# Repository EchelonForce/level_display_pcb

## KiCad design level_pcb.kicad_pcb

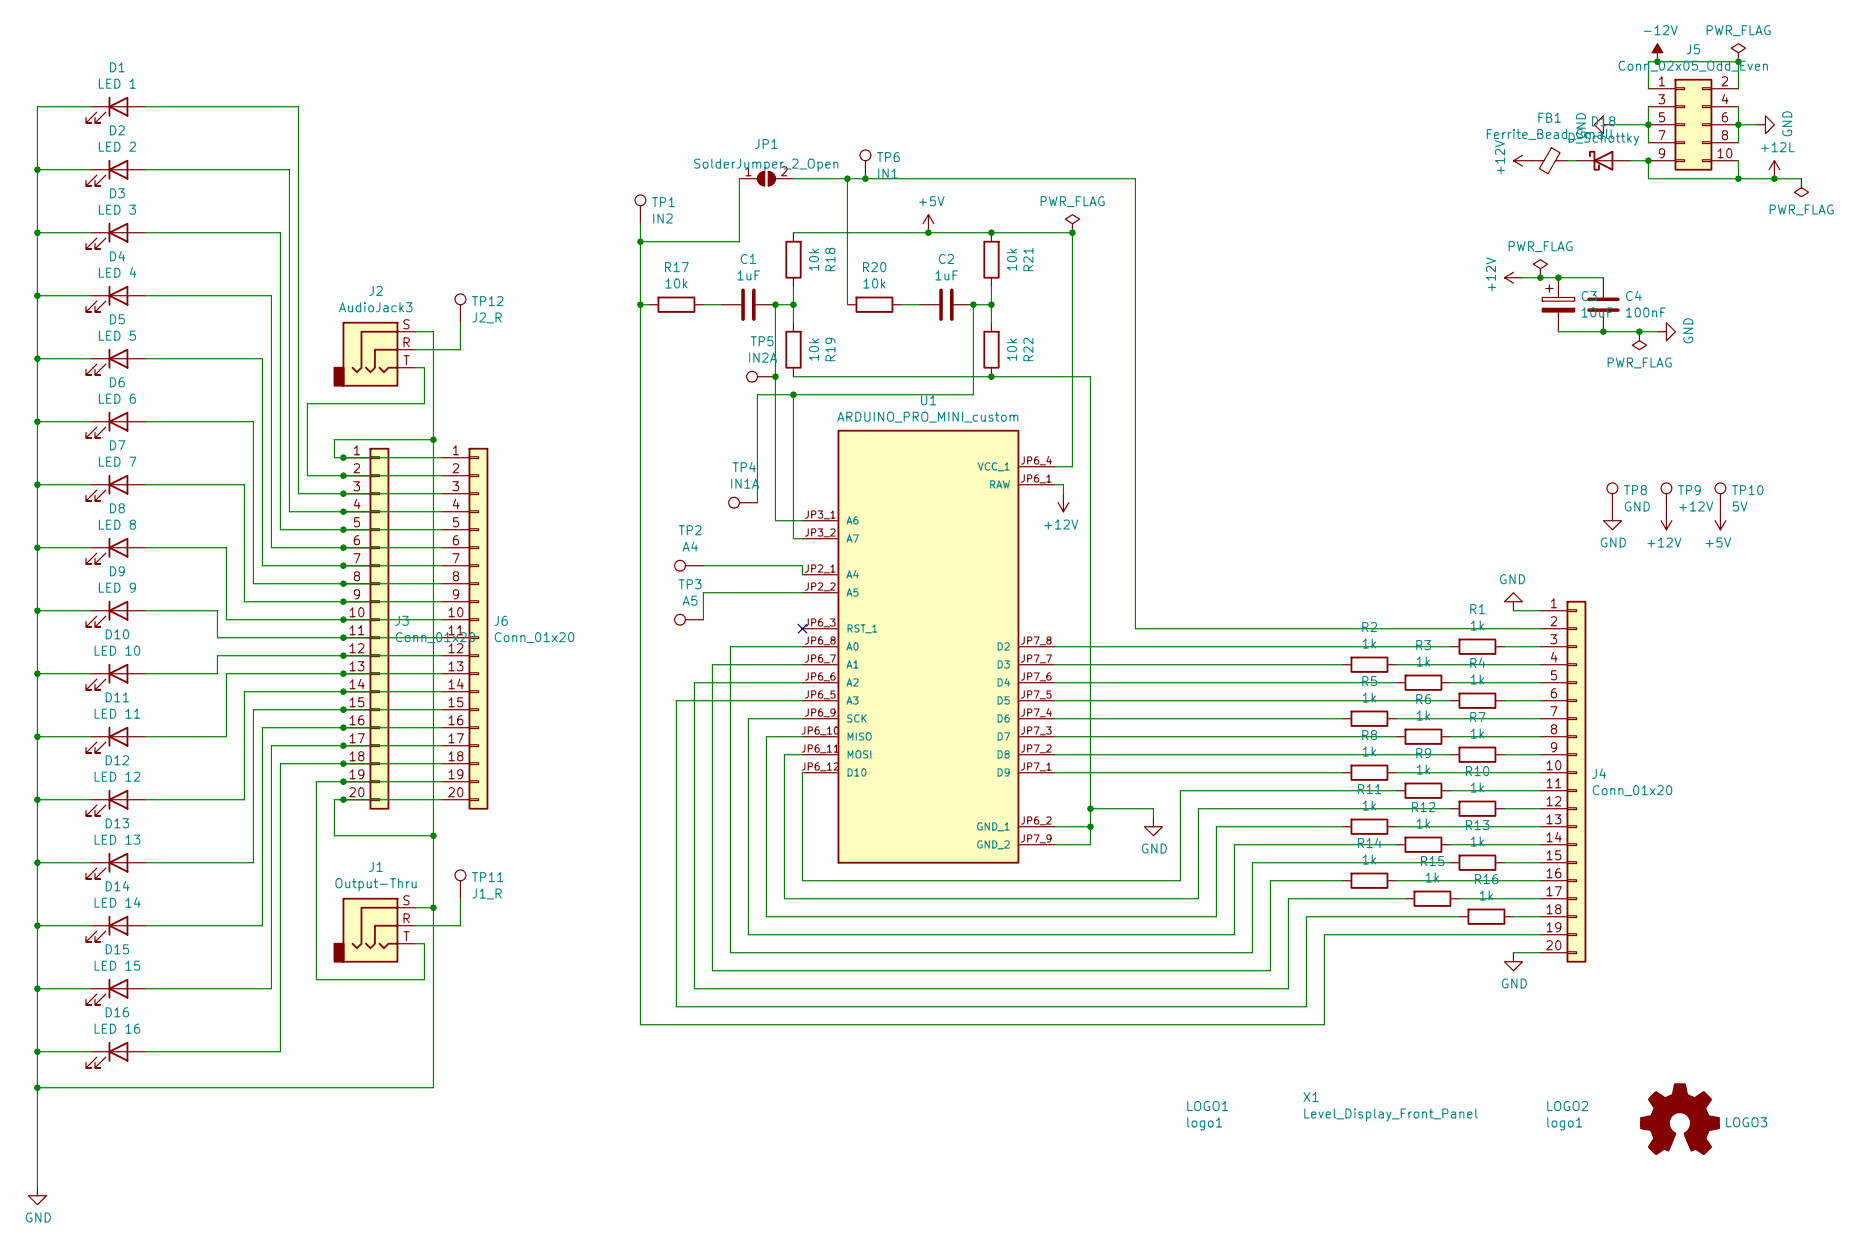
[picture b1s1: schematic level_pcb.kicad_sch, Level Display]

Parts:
C1, C2: 1uF; C_Disc_D6.0mm_W4.4mm_P5.00mm
C3: 10uF; CP_Radial_D5.0mm_P2.50mm
C4: 100nF; C_Disc_D6.0mm_W4.4mm_P5.00mm
D1: LED 1; LED_D3.0mm
D2: LED 2; LED_D3.0mm
D3: LED 3; LED_D3.0mm
D4: LED 4; LED_D3.0mm
D5: LED 5; LED_D3.0mm
D6: LED 6; LED_D3.0mm
D7: LED 7; LED_D3.0mm
D8: LED 8; LED_D3.0mm
D9: LED 9; LED_D3.0mm
D10: LED 10; LED_D3.0mm
D11: LED 11; LED_D3.0mm
D12: LED 12; LED_D3.0mm
D13: LED 13; LED_D3.0mm
D14: LED 14; LED_D3.0mm
D15: LED 15; LED_D3.0mm
D16: LED 16; LED_D3.0mm
D18: D_Schottky; D_DO-15_P10.16mm_Horizontal
FB1: Ferrite_Bead_Small; L_Axial_L7.0mm_D3.3mm_P5.08mm_Vertical_Fastron_MICC
J1: Output-Thru; Jack_2.5mm_MJ-355W_Vertical
J2: AudioJack3; Jack_2.5mm_MJ-355W_Vertical
J3, J6: Conn_01x20; PinHeader_1x20_P2.54mm_Vertical
J4: Conn_01x20; PinSocket_1x20_P2.54mm_Horizontal
J5: Conn_02x05_Odd_Even; IDC-Header_2x05_P2.54mm_Horizontal
JP1: SolderJumper_2_Open; SolderJumper-2_P1.3mm_Open_Pad1.0x1.5mm
LOGO1, LOGO2: logo1; Logo1
LOGO3: Logo_Open_Hardware_Small; OSHW-Symbol_6.7x6mm_SilkScreen
R1, R2, R3, R4, R5, R6, R7, R8, R9, R10, R11, R12, R13, R14, R15, R16: 1k; R_Axial_DIN0204_L3.6mm_D1.6mm_P7.62mm_Horizontal
R17, R18, R19, R20, R21, R22: 10k; R_Axial_DIN0204_L3.6mm_D1.6mm_P7.62mm_Horizontal
TP1: IN2; TestPoint_THTPad_D2.5mm_Drill1.2mm
TP2: A4; TestPoint_THTPad_D2.5mm_Drill1.2mm
TP3: A5; TestPoint_THTPad_D2.5mm_Drill1.2mm
TP4: IN1A; TestPoint_THTPad_D2.5mm_Drill1.2mm
TP5: IN2A; TestPoint_THTPad_D2.5mm_Drill1.2mm
TP6: IN1; TestPoint_THTPad_D2.5mm_Drill1.2mm
TP8: GND; TestPoint_THTPad_2.5x2.5mm_Drill1.2mm
TP9: +12V; TestPoint_THTPad_D2.5mm_Drill1.2mm
TP10: 5V; TestPoint_THTPad_D2.5mm_Drill1.2mm
TP11: J1_R; TestPoint_THTPad_D2.5mm_Drill1.2mm
TP12: J2_R; TestPoint_THTPad_D2.5mm_Drill1.2mm
U1: ARDUINO_PRO_MINI_custom; MODULE_ARDUINO_PRO_MINI_custom; PARTREV N/A
X1: Level_Display_Front_Panel

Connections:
+5V: R18.2, R21.2, TP10.1, U1.JP6_4 (VCC_1)
+12L: D18.2 (A), J5.9, J5.10
+12V: C3.1, C4.2, FB1.2, TP9.1, U1.JP6_1 (RAW)
-12V: J5.1, J5.2
GND: C3.2, C4.1, D1.1 (K), D2.1 (K), D3.1 (K), D4.1 (K), D5.1 (K), D6.1 (K), D7.1 (K), D8.1 (K), D9.1 (K), D10.1 (K), D11.1 (K), D12.1 (K), D13.1 (K), D14.1 (K), D15.1 (K), D16.1 (K), J1.S, J2.S, J3.1, J3.20, J4.1, J4.20, J5.3, J5.4, J5.5, J5.6, J5.7, J5.8, J6.1, J6.20, R19.1, R22.1, TP8.1, U1.JP6_2 (GND_1), U1.JP7_9 (GND_2)
unnamed: C1.1, R18.1, R19.2, TP5.1, U1.JP3_1 (A6)
unnamed: C1.2, R17.1
unnamed: C2.1, R21.1, R22.2, TP4.1, U1.JP3_2 (A7)
unnamed: C2.2, R20.1
unnamed: D1.2 (A), J3.3, J6.3
unnamed: D2.2 (A), J3.4, J6.4
unnamed: D3.2 (A), J3.5, J6.5
unnamed: D4.2 (A), J3.6, J6.6
unnamed: D5.2 (A), J3.7, J6.7
unnamed: D6.2 (A), J3.8, J6.8
unnamed: D7.2 (A), J3.9, J6.9
unnamed: D8.2 (A), J3.10, J6.10
unnamed: D9.2 (A), J3.11, J6.11
unnamed: D10.2 (A), J3.12, J6.12
unnamed: D11.2 (A), J3.13, J6.13
unnamed: D12.2 (A), J3.14, J6.14
unnamed: D13.2 (A), J3.15, J6.15
unnamed: D14.2 (A), J3.16, J6.16
unnamed: D15.2 (A), J3.17, J6.17
unnamed: D16.2 (A), J3.18, J6.18
unnamed: D18.1 (K), FB1.1
unnamed: J1.R, TP11.1
unnamed: J1.T, J3.19, J6.19
unnamed: J2.R, TP12.1
unnamed: J2.T, J3.2, J6.2
unnamed: J4.2, JP1.2 (B), R20.2, TP6.1
unnamed: J4.3, R1.1
unnamed: J4.4, R2.1
unnamed: J4.5, R3.1
unnamed: J4.6, R4.1
unnamed: J4.7, R5.1
unnamed: J4.8, R6.1
unnamed: J4.9, R7.1
unnamed: J4.10, R8.1
unnamed: J4.11, R9.1
unnamed: J4.12, R10.1
unnamed: J4.13, R11.1
unnamed: J4.14, R12.1
unnamed: J4.15, R13.1
unnamed: J4.16, R14.1
unnamed: J4.17, R15.1
unnamed: J4.18, R16.1
unnamed: J4.19, JP1.1 (A), R17.2, TP1.1
unnamed: R1.2, U1.JP7_8 (D2)
unnamed: R2.2, U1.JP7_7 (D3)
unnamed: R3.2, U1.JP7_6 (D4)
unnamed: R4.2, U1.JP7_5 (D5)
unnamed: R5.2, U1.JP7_4 (D6)
unnamed: R6.2, U1.JP7_3 (D7)
unnamed: R7.2, U1.JP7_2 (D8)
unnamed: R8.2, U1.JP7_1 (D9)
unnamed: R9.2, U1.JP6_12 (D10)
unnamed: R10.2, U1.JP6_11 (MOSI)
unnamed: R11.2, U1.JP6_10 (MISO)
unnamed: R12.2, U1.JP6_9 (SCK)
unnamed: R13.2, U1.JP6_8 (A0)
unnamed: R14.2, U1.JP6_7 (A1)
unnamed: R15.2, U1.JP6_6 (A2)
unnamed: R16.2, U1.JP6_5 (A3)
unnamed: TP2.1, U1.JP2_1 (A4)
unnamed: TP3.1, U1.JP2_2 (A5)

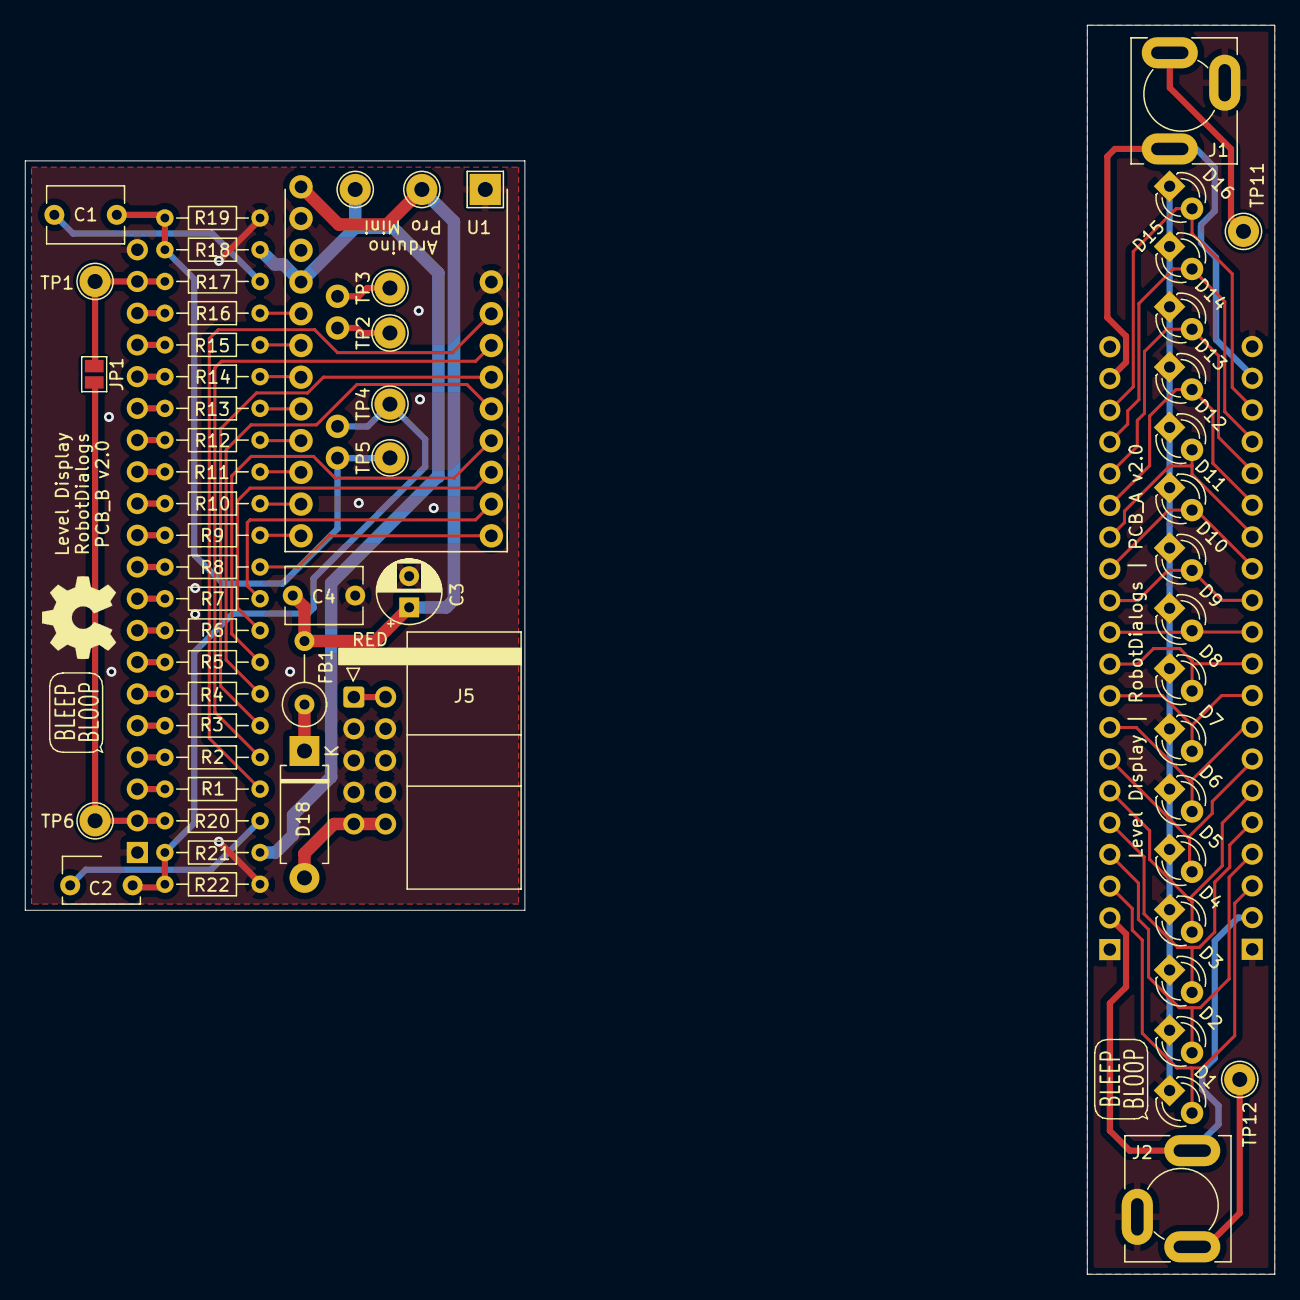
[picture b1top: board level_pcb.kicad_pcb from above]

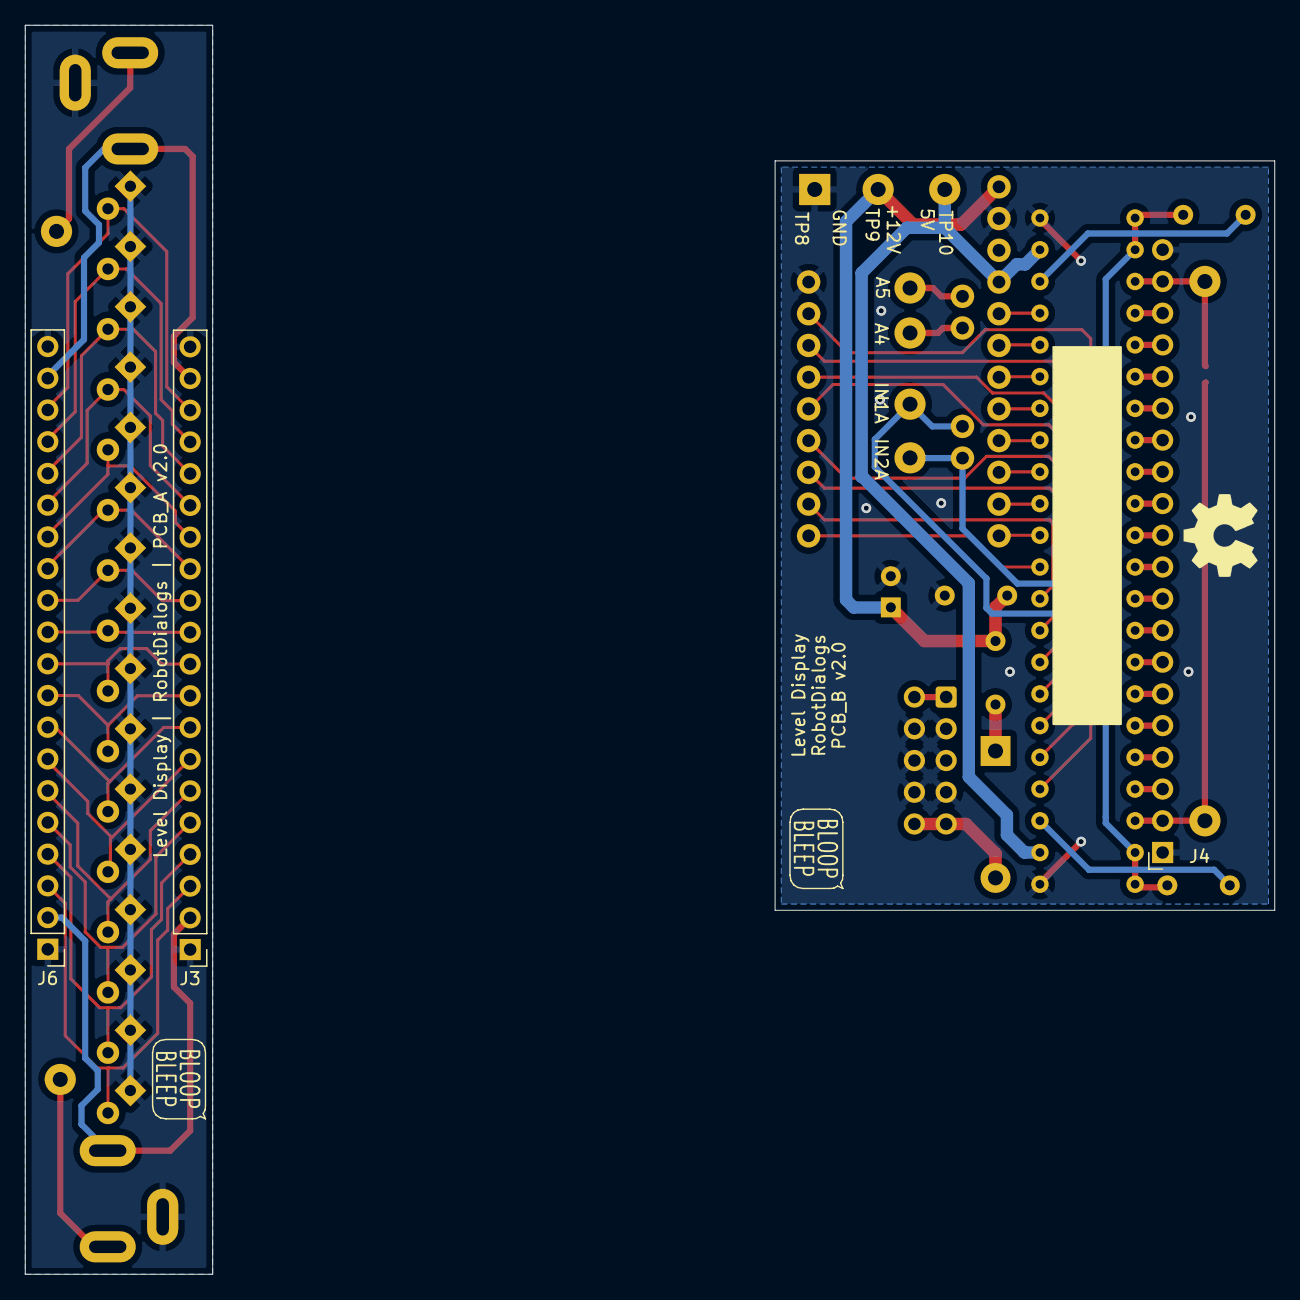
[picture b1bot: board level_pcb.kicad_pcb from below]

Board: 2 copper layers, 100.0 x 100.0 mm, 70 parts (7 on the bottom side), 66 nets.

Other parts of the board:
LOGO1#2, LOGO2#2: logo1; Logo1
LOGO3#2: Logo_Open_Hardware_Small; OSHW-Symbol_6.7x6mm_SilkScreen

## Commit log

2022-02-13 Initial Commit
    Added .gitignore
2022-02-13 Version 1 PCB as ordered
    Requires
    https://github.com/Duckle29/kicad-libraries/blob/master/arduino-pro-mini.lib
2022-02-13 Version 2 PCB as ordered
    Switch to KiCAD v6
